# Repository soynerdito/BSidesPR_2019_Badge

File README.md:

# Badge for BSides PR 2019

This is a DIY badge for all participants, promoting the hand on soldering experience that everyone likes. A security conference is about learning by doing and sharing.

In the spirit of sharing, files in this repo can be used as you please and I expect no retribution.
You and only you are responsible for what you do with this project. Enjoy.

This badge is not a product for sale in any way, it's for sharing and learning. Have a good day.

[Read the docs](https://bsidesprbadge2019.readthedocs.io/)

## 3D Render of the badge
Render from KiCad.

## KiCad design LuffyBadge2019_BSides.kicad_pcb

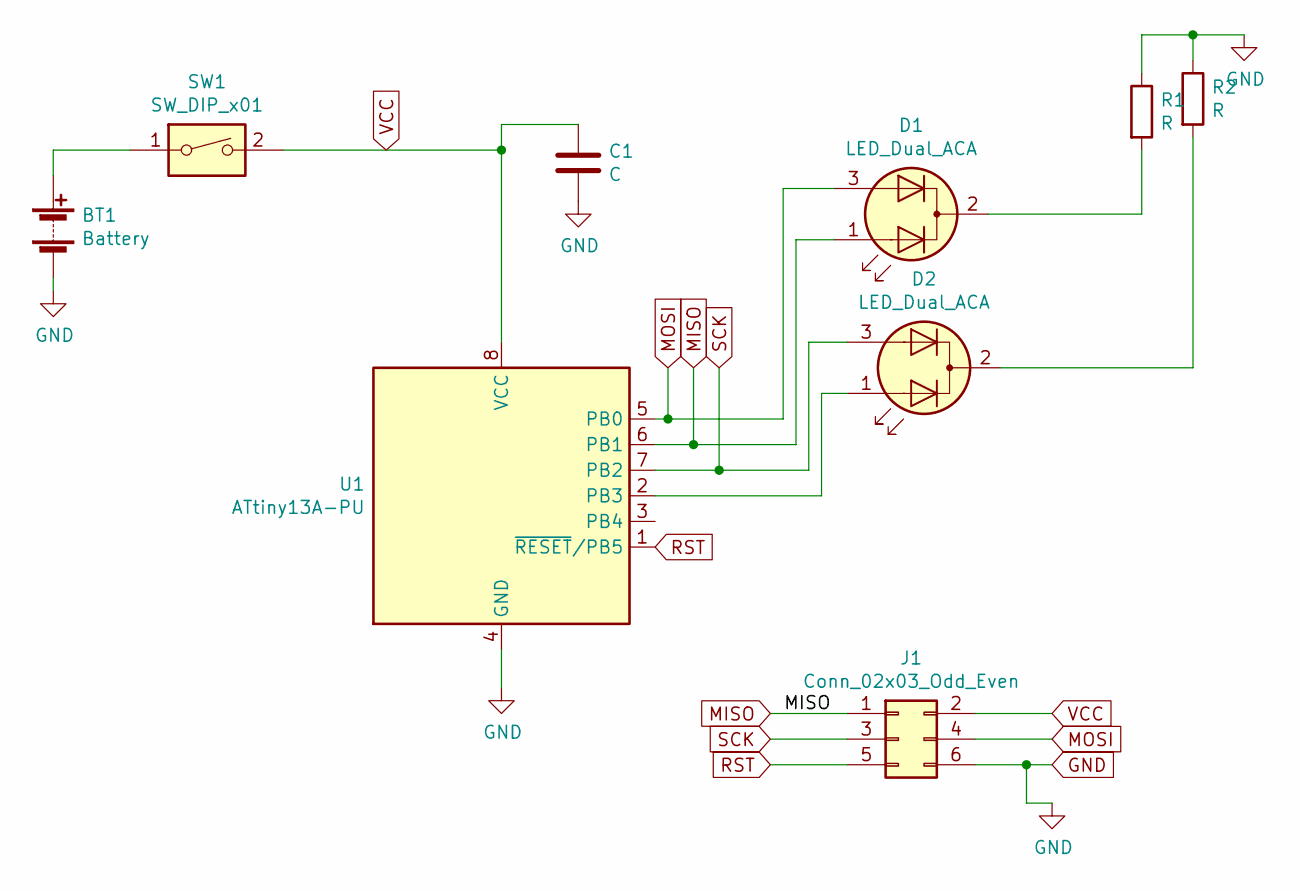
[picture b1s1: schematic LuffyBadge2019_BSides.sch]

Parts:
BT1: Battery; Keystone_103_1x20mm-CoinCell
C1: C; C_0603_HandSoldering
D1, D2: LED_Dual_ACA; LED_D3.0mm-3
J1: Conn_02x03_Odd_Even; Pin_Header_Straight_2x03_Pitch2.54mm
R1, R2: R; PR-D1.8_L3.3MM
SW1: SW_DIP_x01; SW_DIP_x1_W7.62mm_Slide
U1: ATtiny13A-PU; PDIP-8

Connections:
GND: BT1.2 (-), C1.2, J1.6, R1.1, R2.1, U1.4 (GND)
MISO: D1.1 (A1), J1.1, U1.6 (PB1)
MOSI: D1.3 (A2), J1.4, U1.5 (PB0)
unnamed: BT1.1 (+), SW1.1
unnamed: D1.2 (K), R1.2
unnamed: D2.1 (A1), U1.2 (PB3)
unnamed: D2.2 (K), R2.2
RST: J1.5, U1.1 (~RESET~/PB5)
SCK: D2.3 (A2), J1.3, U1.7 (PB2)
VCC: C1.1, J1.2, SW1.2, U1.8 (VCC)

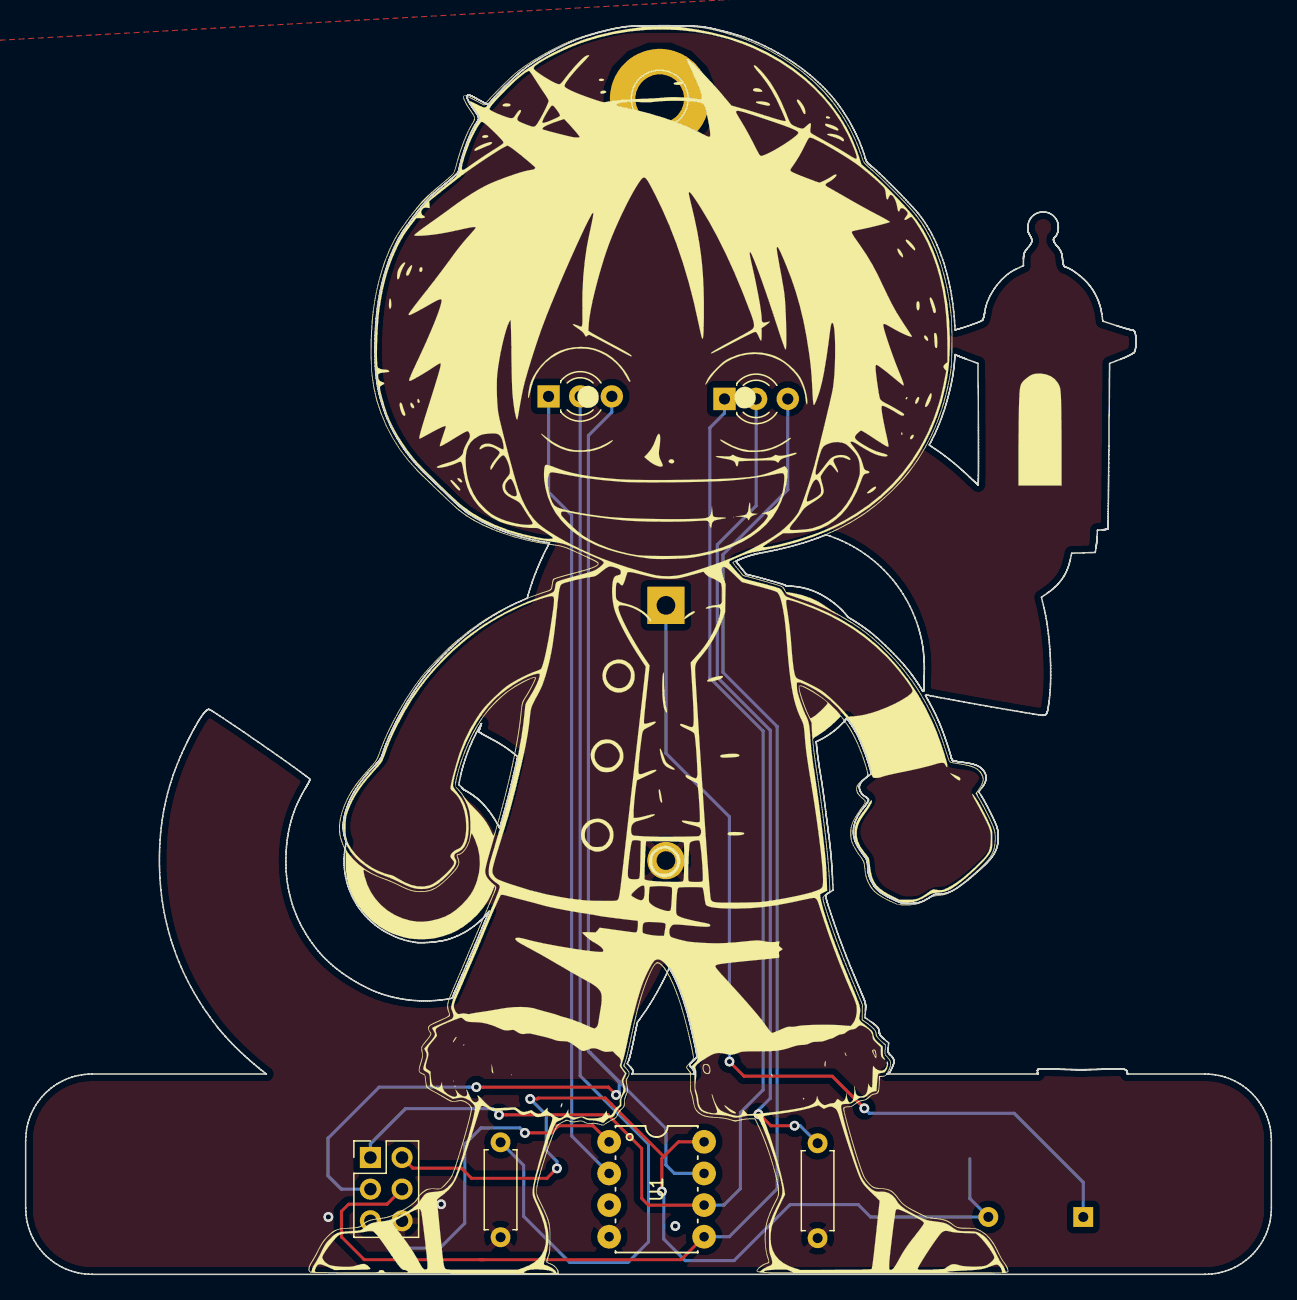
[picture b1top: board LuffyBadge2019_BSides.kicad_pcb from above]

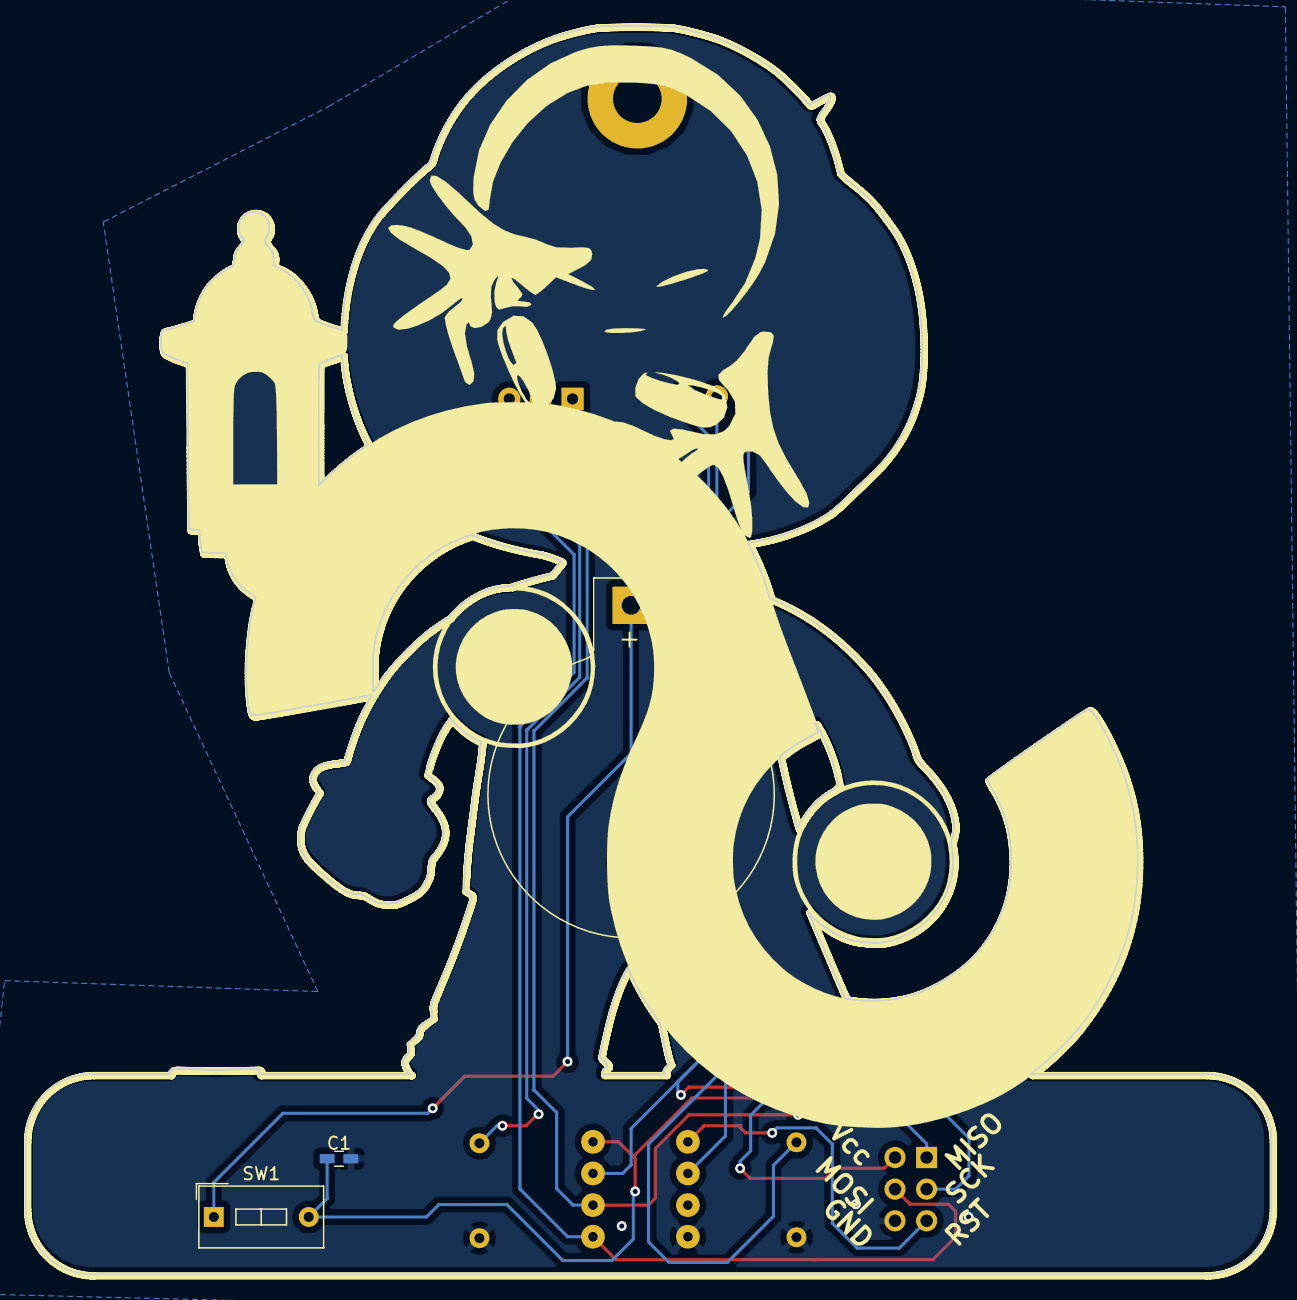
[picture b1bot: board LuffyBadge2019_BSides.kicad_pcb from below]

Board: 2 copper layers, 100.0 x 100.2 mm, 9 parts (3 on the bottom side), 10 nets.

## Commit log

2019-07-09 Adding gitignore
2019-07-09 Adding License
2019-07-09 applying gitignore
2019-07-09 Adding readme
2019-07-09 renaming some files
2019-07-09 Adding all related files into a more organized structure
2019-07-09 Updating readme
2019-08-06 Fix vcc path on right leg
2019-08-06 Just saved the files in case of
2019-09-14 adding docs
2019-09-14 just adding a bit of documentation, starting up
2019-09-14 changing heading, left from copy paste... oops
2019-10-09 Adding images to help
2019-10-09 image link
2019-10-09 refactoring typo
2019-10-09 image name error
2019-10-09 Adding samples
2019-10-09 Adding link to read the docs
2019-10-09 quick fix, typo. Could be better but.. oh well
